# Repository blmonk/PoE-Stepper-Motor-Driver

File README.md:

# PoE-Stepper-Motor-Driver
ECE445 Senior Design

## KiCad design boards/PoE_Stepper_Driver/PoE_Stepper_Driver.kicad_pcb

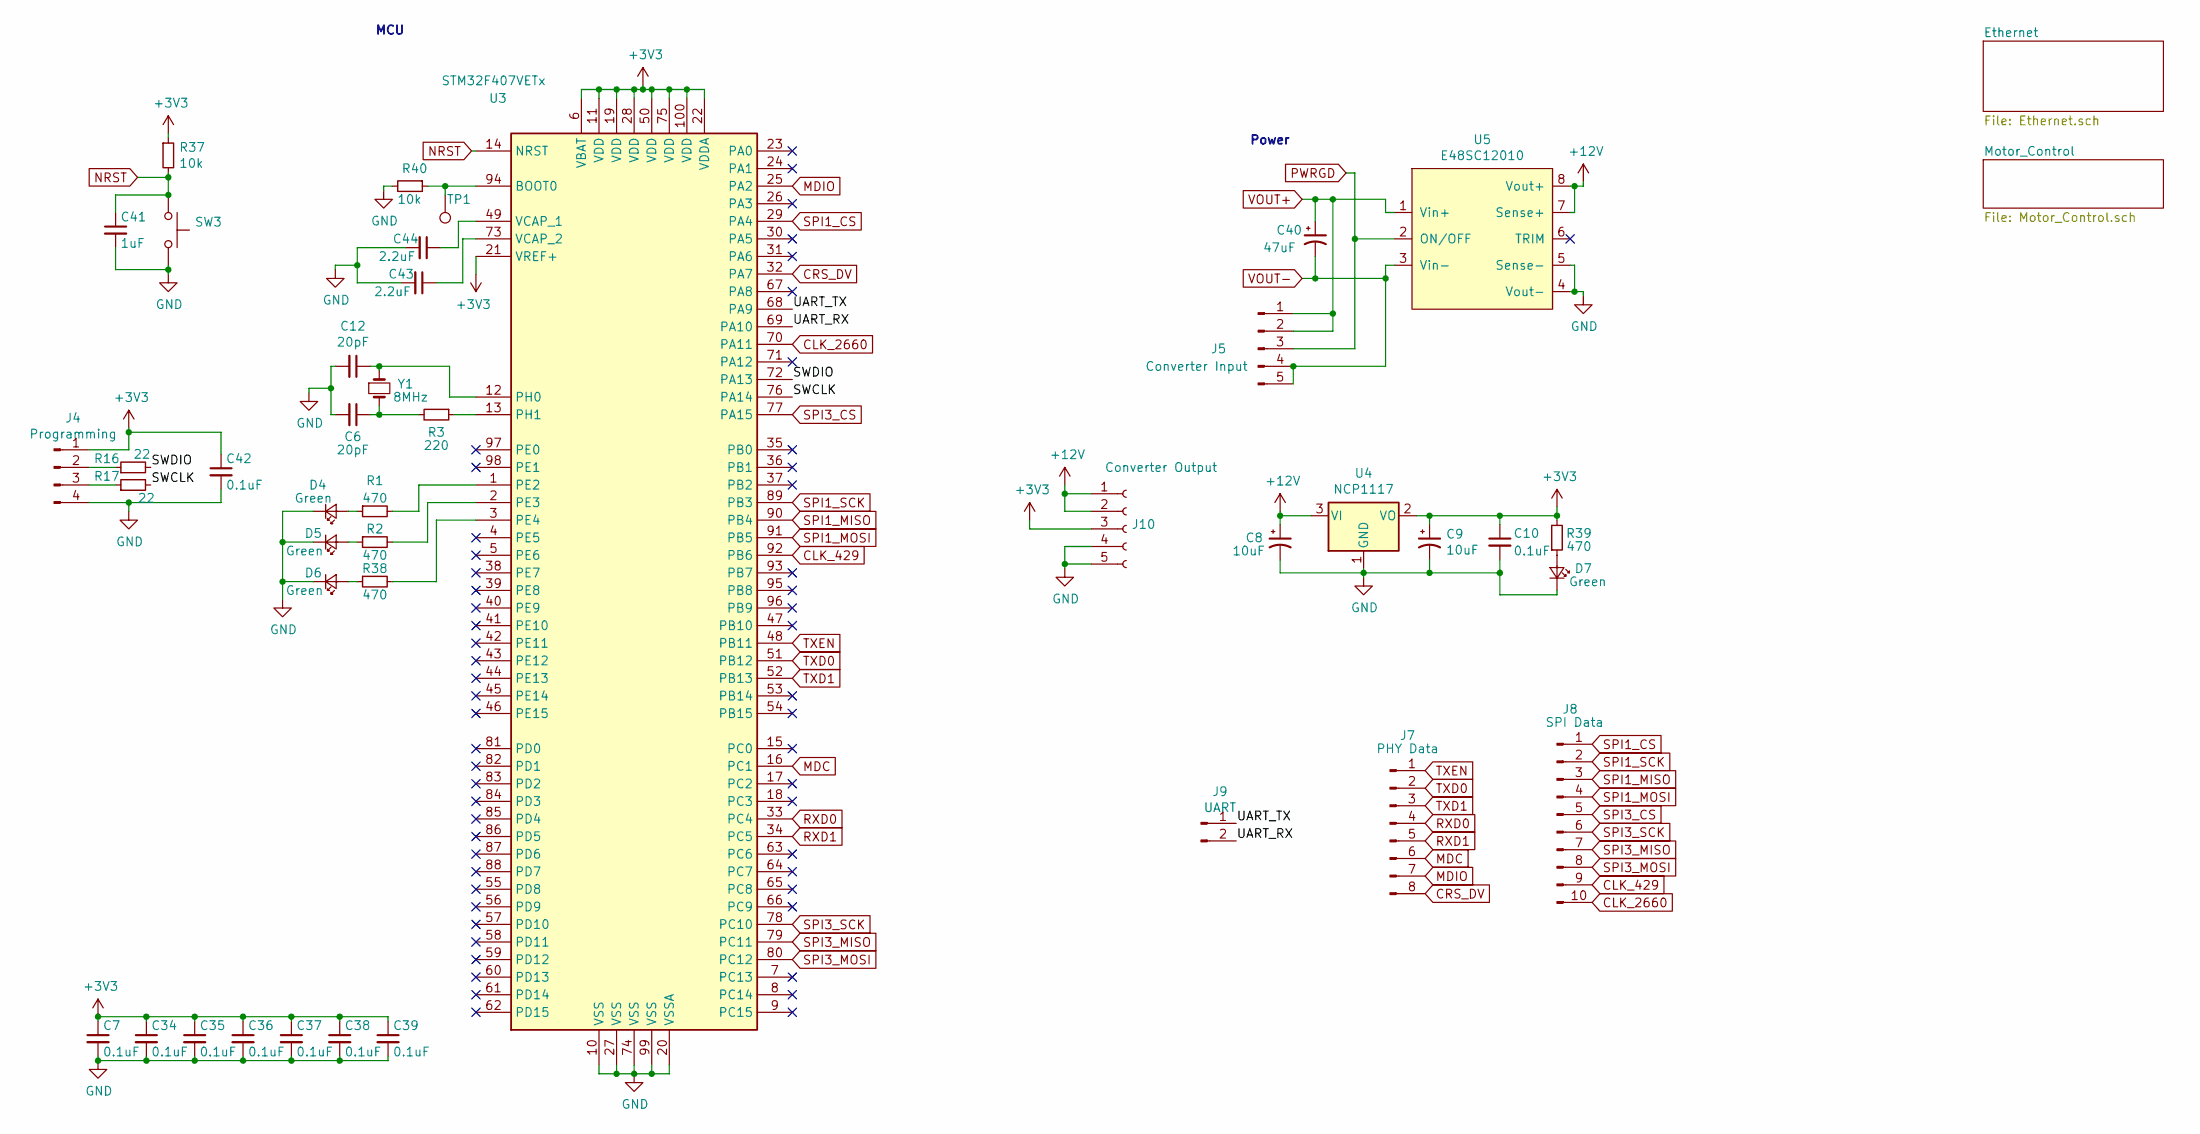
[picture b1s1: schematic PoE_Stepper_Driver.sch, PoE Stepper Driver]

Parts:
C6, C12: 20pF; C_0603_1608Metric_Pad1.05x0.95mm_HandSolder
C7, C10, C34, C35, C36, C37, C38, C39, C42: 0.1uF; C_0805_2012Metric_Pad1.15x1.40mm_HandSolder
C8, C9: 10uF; CP_Elec_6.3x5.4
C40: 47uF; CP_Radial_D8.0mm_P3.50mm
C41: 1uF; C_0805_2012Metric_Pad1.15x1.40mm_HandSolder
C43, C44: 2.2uF; C_0603_1608Metric_Pad1.05x0.95mm_HandSolder
D4, D5, D6, D7: Green; LED_0805_2012Metric_Pad1.15x1.40mm_HandSolder
J4: Programming; PinHeader_1x04_P2.54mm_Vertical
J5: Converter Input; PinHeader_1x05_P2.54mm_Vertical
J7: PHY Data; PinHeader_2x04_P2.54mm_Vertical
J8: SPI Data; PinHeader_2x05_P2.54mm_Vertical
J9: UART; PinHeader_1x02_P2.54mm_Vertical
J10: Converter Output; PinHeader_1x05_P2.54mm_Vertical
R1, R2, R38, R39: 470; R_0805_2012Metric_Pad1.15x1.40mm_HandSolder
R3: 220; R_0603_1608Metric_Pad1.05x0.95mm_HandSolder
R16, R17: 22; R_0805_2012Metric_Pad1.15x1.40mm_HandSolder
R37, R40: 10k; R_0805_2012Metric_Pad1.15x1.40mm_HandSolder
SW3: SW_Push; SW_SPST_B3S-1000
TP1: BOOT0; TestPoint_Pad_1.0x1.0mm
U3: STM32F407VETx; LQFP-100_14x14mm_P0.5mm
U4: NCP1117; SOT-223-3_TabPin2
U5: E48SC12010
Y1: 8MHz; Crystal_HC49-4H_Vertical

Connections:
+3V3: C7.1, C9.1, C10.1, C34.1, C35.1, C36.1, C37.1, C38.1, C39.1, C42.1, J4.1, J10.3, R37.1, R39.2, U3.6 (VBAT), U3.11 (VDD), U3.19 (VDD), U3.21 (VREF+), U3.22 (VDDA), U3.28 (VDD), U3.50 (VDD), U3.75 (VDD), U3.100 (VDD), U4.2 (VO); also elsewhere on the board
+12V: C8.1, J10.1, J10.2, U4.3 (VI), U5.7 (Sense+), U5.8 (Vout+); also elsewhere on the board
/SWCLK: R17.2, U3.76 (PA14)
/SWDIO: R16.2, U3.72 (PA13)
/UART_RX: J9.2, U3.69 (PA10)
/UART_TX: J9.1, U3.68 (PA9)
CLK_429: J8.9, U3.92 (PB6); also elsewhere on the board
CLK_2660: J8.10, U3.70 (PA11); also elsewhere on the board
CRS_DV: J7.8, U3.32 (PA7); also elsewhere on the board
GND: C6.2, C7.2, C8.2, C9.2, C10.2, C12.2, C34.2, C35.2, C36.2, C37.2, C38.2, C39.2, C41.2, C42.2, C43.2, C44.2, D4.1 (K), D5.1 (K), D6.1 (K), D7.1 (K), J4.4, J10.4, J10.5, R40.2, SW3.2, U3.10 (VSS), U3.20 (VSSA), U3.27 (VSS), U3.74 (VSS), U3.99 (VSS), U4.1 (GND), U5.4 (Vout-), U5.5 (Sense-); also elsewhere on the board
MDC: J7.6, U3.16 (PC1); also elsewhere on the board
MDIO: J7.7, U3.25 (PA2); also elsewhere on the board
NRST: C41.1, R37.2, SW3.1, U3.14 (NRST); also elsewhere on the board
unnamed: C6.1, R3.2, Y1.2
unnamed: C12.1, U3.12 (PH0), Y1.1
unnamed: C43.1, U3.73 (VCAP_2)
unnamed: C44.1, U3.49 (VCAP_1)
unnamed: D4.2 (A), R1.1
unnamed: D5.2 (A), R2.1
unnamed: D6.2 (A), R38.1
unnamed: D7.2 (A), R39.1
unnamed: J4.2, R16.1
unnamed: J4.3, R17.1
unnamed: R1.2, U3.1 (PE2)
unnamed: R2.2, U3.2 (PE3)
unnamed: R3.1, U3.13 (PH1)
unnamed: R38.2, U3.3 (PE4)
unnamed: R40.1, TP1.1, U3.94 (BOOT0)
PWRGD: J5.3, U5.2 (ON/OFF); also elsewhere on the board
RXD0: J7.4, U3.33 (PC4); also elsewhere on the board
RXD1: J7.5, U3.34 (PC5); also elsewhere on the board
SPI1_CS: J8.1, U3.29 (PA4); also elsewhere on the board
SPI1_MISO: J8.3, U3.90 (PB4); also elsewhere on the board
SPI1_MOSI: J8.4, U3.91 (PB5); also elsewhere on the board
SPI1_SCK: J8.2, U3.89 (PB3); also elsewhere on the board
TXD0: J7.2, U3.51 (PB12); also elsewhere on the board
TXD1: J7.3, U3.52 (PB13); also elsewhere on the board
TXEN: J7.1, U3.48 (PB11); also elsewhere on the board
VOUT+: C40.1, J5.1, J5.2, U5.1 (Vin+); also elsewhere on the board
VOUT-: C40.2, J5.4, J5.5, U5.3 (Vin-); also elsewhere on the board

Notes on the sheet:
Power
MCU

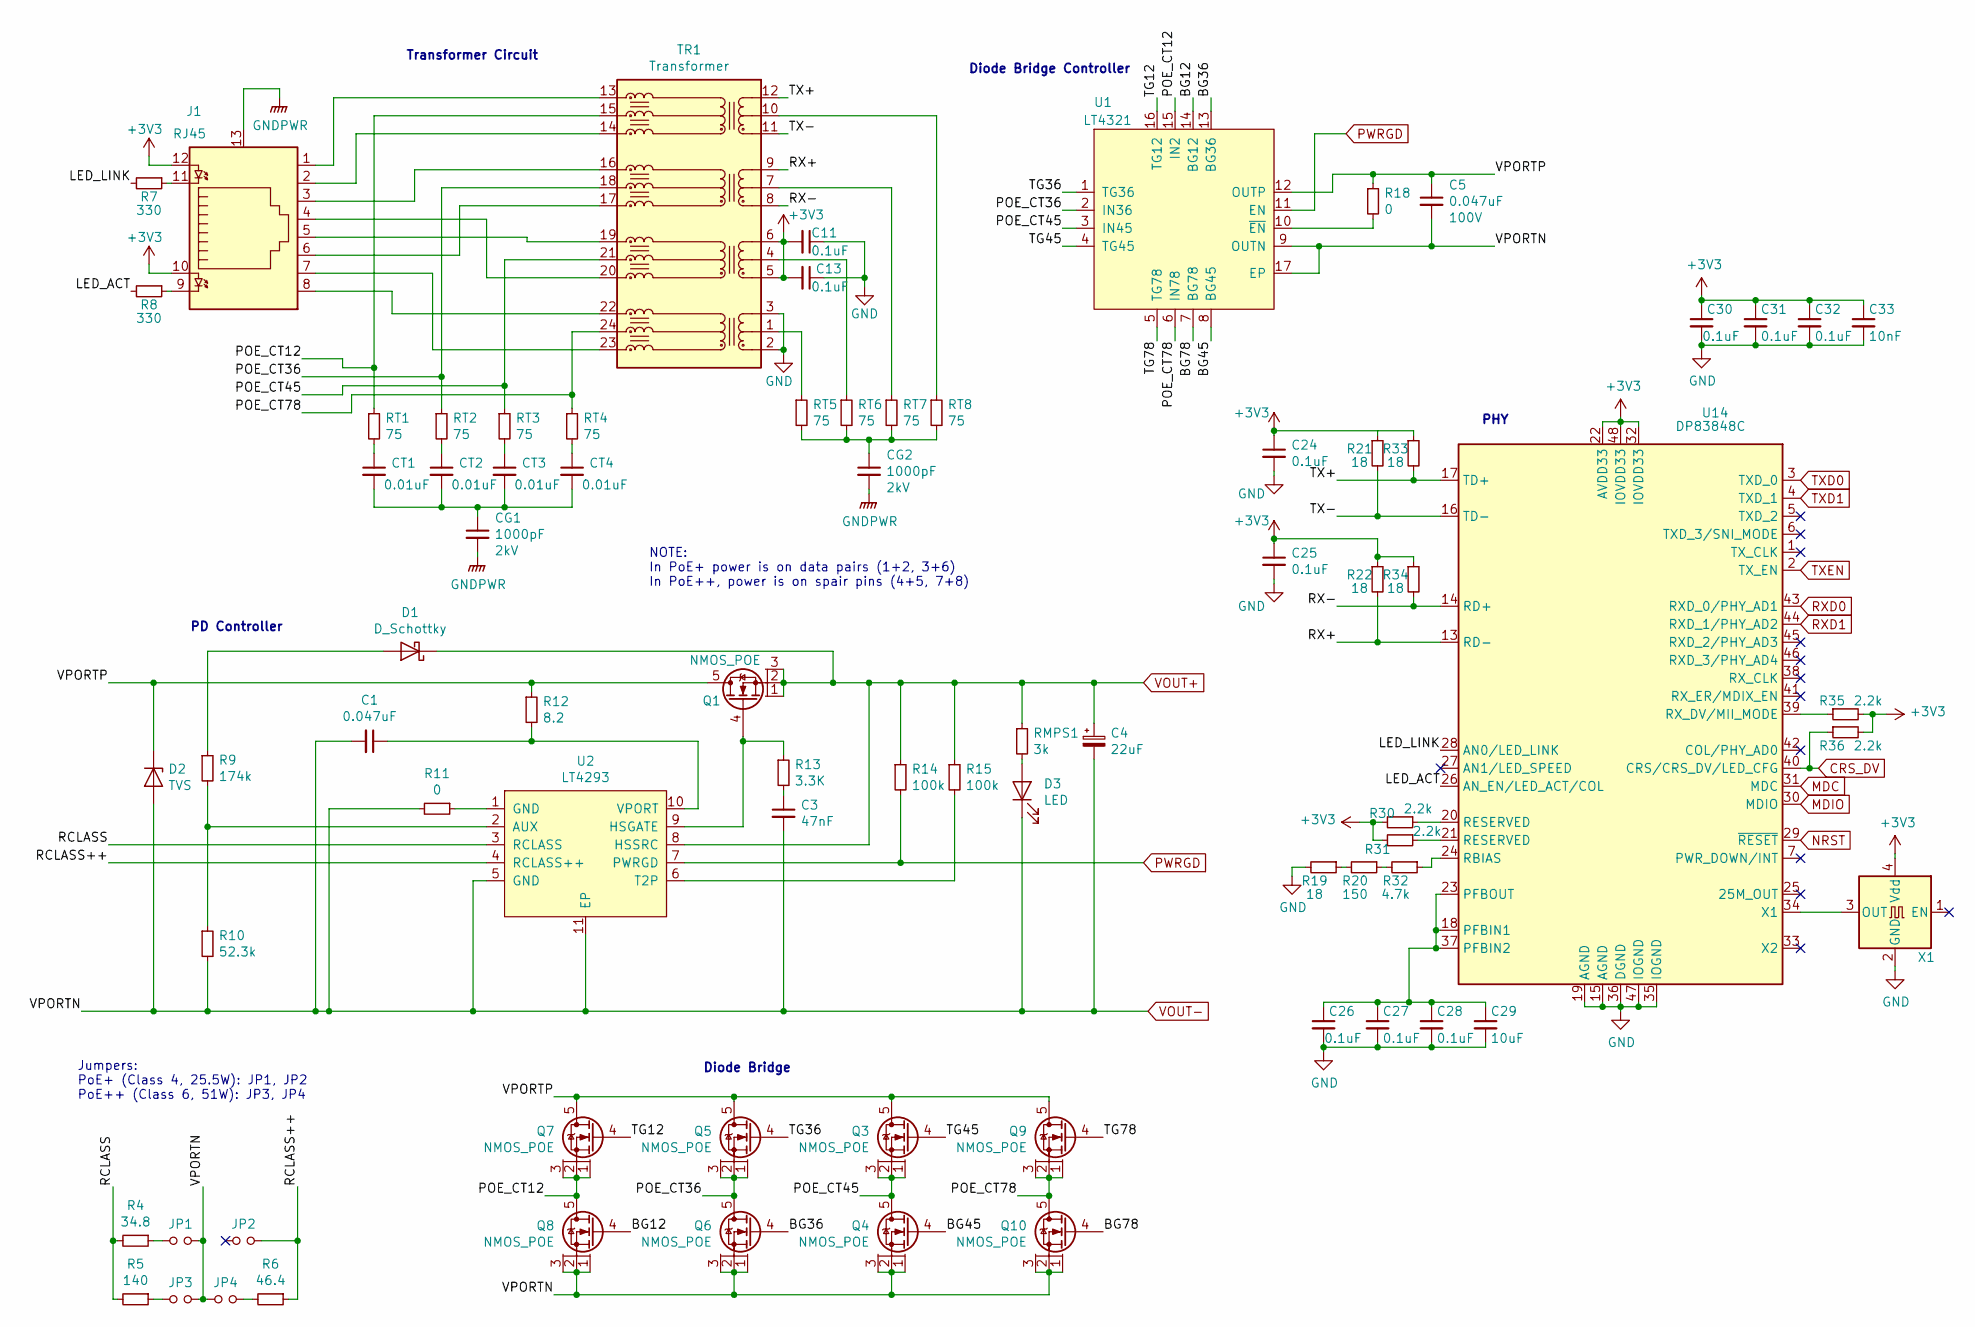
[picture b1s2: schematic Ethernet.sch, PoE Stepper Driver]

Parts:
C1: 0.047uF; C_0603_1608Metric_Pad1.05x0.95mm_HandSolder
C3: 47nF; C_0805_2012Metric_Pad1.15x1.40mm_HandSolder
C4: 22uF; CP_Elec_8x10.5
C5: 0.047uF; C_0603_1608Metric_Pad1.05x0.95mm_HandSolder; Voltage 100V
C11, C13, C24, C25, C26, C27, C28, C30, C31, C32: 0.1uF; C_0805_2012Metric_Pad1.15x1.40mm_HandSolder
C29: 10uF; C_0805_2012Metric_Pad1.15x1.40mm_HandSolder
C33: 10nF; C_0805_2012Metric_Pad1.15x1.40mm_HandSolder
CG1, CG2: 1000pF; C_1812_4532Metric_Pad1.30x3.40mm_HandSolder; Voltage 2kV
CT1, CT2, CT3, CT4: 0.01uF; C_0805_2012Metric_Pad1.15x1.40mm_HandSolder
D1: D_Schottky; D_SOD-128
D2: TVS; D_SOD-128
D3: LED; LED_0805_2012Metric_Pad1.15x1.40mm_HandSolder
J1: RJ45; RJ45_Amphenol_RJMG1BD3B8K1ANR
JP1, JP2, JP3, JP4: Jumper_NO_Small; PinHeader_1x02_P2.54mm_Vertical
Q1, Q3, Q4, Q5, Q6, Q7, Q8, Q9, Q10: NMOS_POE; LFPAK33
R4: 34.8; R_0805_2012Metric_Pad1.15x1.40mm_HandSolder
R5: 140; R_0805_2012Metric_Pad1.15x1.40mm_HandSolder
R6: 46.4; R_0805_2012Metric_Pad1.15x1.40mm_HandSolder
R7, R8: 330; R_0805_2012Metric_Pad1.15x1.40mm_HandSolder
R9: 174k; R_0603_1608Metric_Pad1.05x0.95mm_HandSolder
R10: 52.3k; R_0603_1608Metric_Pad1.05x0.95mm_HandSolder
R11, R18: 0; R_0603_1608Metric_Pad1.05x0.95mm_HandSolder
R12: 8.2; R_0805_2012Metric_Pad1.15x1.40mm_HandSolder
R13: 3.3K; R_0603_1608Metric_Pad1.05x0.95mm_HandSolder
R14, R15: 100k; R_0603_1608Metric_Pad1.05x0.95mm_HandSolder
R19, R21, R22, R33, R34: 18; R_0805_2012Metric_Pad1.15x1.40mm_HandSolder
R20: 150; R_0805_2012Metric_Pad1.15x1.40mm_HandSolder
R30, R31, R35, R36: 2.2k; R_0805_2012Metric_Pad1.15x1.40mm_HandSolder
R32: 4.7k; R_0805_2012Metric_Pad1.15x1.40mm_HandSolder
RMPS1: 3k; R_2512_6332Metric_Pad1.52x3.35mm_HandSolder
RT1, RT2, RT3, RT4, RT5, RT6, RT7, RT8: 75; R_0603_1608Metric_Pad1.05x0.95mm_HandSolder
TR1: Transformer; PoE_Transformer
U1: LT4321; QFN-16-1EP_4x4mm_P0.65mm_EP2.15x2.15mm
U2: LT4293; MSOP-10_3x3mm_P0.5mm
U14: DP83848C; LQFP-48_7x7mm_P0.5mm
X1: SXO53C

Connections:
+3V3: C11.2, C13.2, C24.1, C25.1, C30.1, C31.1, C32.1, C33.1, J1.10, J1.12, R21.1, R22.1, R30.2, R31.2, R33.1, R34.1, R35.2, R36.2, TR1.5 (TD2+), TR1.6 (TD2-), U14.22 (AVDD33), U14.32 (IOVDD33), U14.48 (IOVDD33), X1.4 (Vdd); also elsewhere on the board
/Ethernet/BG12: Q8.4, U1.14 (BG12)
/Ethernet/BG36: Q6.4, U1.13 (BG36)
/Ethernet/BG45: Q4.4, U1.8 (BG45)
/Ethernet/BG78: Q10.4, U1.7 (BG78)
/Ethernet/LED_ACT: R8.2, U14.26 (AN_EN/LED_ACT/COL)
/Ethernet/LED_LINK: R7.2, U14.28 (AN0/LED_LINK)
/Ethernet/POE_CT12: Q7.1, Q7.2, Q7.3, Q8.5, RT1.1, TR1.15 (MCT4), U1.15 (IN2)
/Ethernet/POE_CT36: Q5.1, Q5.2, Q5.3, Q6.5, RT2.1, TR1.18 (MCT3), U1.2 (IN36)
/Ethernet/POE_CT45: Q3.1, Q3.2, Q3.3, Q4.5, RT3.1, TR1.21 (MCT2), U1.3 (IN45)
/Ethernet/POE_CT78: Q9.1, Q9.2, Q9.3, Q10.5, RT4.1, TR1.24 (MTC1), U1.6 (IN78)
/Ethernet/RCLASS: R4.2, R5.2, U2.3 (RCLASS)
/Ethernet/RCLASS++: JP2.2, R6.1, U2.4 (RCLASS++)
/Ethernet/RX+: R22.2, TR1.9 (TD3-), U14.13 (RD-)
/Ethernet/RX-: R34.2, TR1.8 (TD3+), U14.14 (RD+)
/Ethernet/TG12: Q7.4, U1.16 (TG12)
/Ethernet/TG36: Q5.4, U1.1 (TG36)
/Ethernet/TG45: Q3.4, U1.4 (TG45)
/Ethernet/TG78: Q9.4, U1.5 (TG78)
/Ethernet/TX+: R33.2, TR1.12 (TD4-), U14.17 (TD+)
/Ethernet/TX-: R21.2, TR1.11 (TD4+), U14.16 (TD-)
/Ethernet/VPORTP: C5.1, D2.1 (K), Q1.5, Q3.5, Q5.5, Q7.5, Q9.5, R12.1, R18.1, U1.12 (OUTP)
CRS_DV: R36.1, U14.40 (CRS/CRS_DV/LED_CFG); also elsewhere on the board
GND: C11.1, C13.1, C24.2, C25.2, C26.2, C27.2, C28.2, C29.2, C30.2, C31.2, C32.2, C33.2, R19.2, TR1.2 (TD1+), TR1.3 (TD1-), U14.15 (AGND), U14.19 (AGND), U14.35 (IOGND), U14.36 (DGND), U14.47 (IOGND), X1.2 (GND); also elsewhere on the board
GNDPWR: CG1.2, CG2.2, J1.13
MDC: U14.31 (MDC); also elsewhere on the board
MDIO: U14.30 (MDIO); also elsewhere on the board
NRST: U14.29 (~RESET~); also elsewhere on the board
unnamed: C1.1, R12.2, U2.10 (VPORT)
unnamed: C3.1, R13.2
unnamed: C26.1, C27.1, C28.1, C29.1, U14.18 (PFBIN1), U14.23 (PFBOUT), U14.37 (PFBIN2)
unnamed: CG1.1, CT1.2, CT2.2, CT3.2, CT4.2
unnamed: CG2.1, RT5.2, RT6.2, RT7.2, RT8.2
unnamed: CT1.1, RT1.2
unnamed: CT2.1, RT2.2
unnamed: CT3.1, RT3.2
unnamed: CT4.1, RT4.2
unnamed: D1.2 (A), R9.1
unnamed: D3.2 (A), RMPS1.2
unnamed: J1.1, TR1.13 (MX4-)
unnamed: J1.2, TR1.14 (MX4+)
unnamed: J1.3, TR1.16 (MTX3-)
unnamed: J1.4, TR1.20 (MTX2+)
unnamed: J1.5, TR1.19 (MTX2-)
unnamed: J1.6, TR1.17 (MTX3+)
unnamed: J1.7, TR1.23 (MTX1+)
unnamed: J1.8, TR1.22 (MTX1-)
unnamed: J1.9, R8.1
unnamed: J1.11, R7.1
unnamed: JP1.1, R4.1
unnamed: JP3.1, R5.1
unnamed: JP4.2, R6.2
unnamed: Q1.4, R13.1, U2.9 (HSGATE)
unnamed: R9.2, R10.1, U2.2 (AUX)
unnamed: R11.1, U2.1 (GND)
unnamed: R15.2, U2.6 (T2P)
unnamed: R18.2, U1.10 (~EN)
unnamed: R19.1, R20.2
unnamed: R20.1, R32.2
unnamed: R30.1, U14.20 (RESERVED)
unnamed: R31.1, U14.21 (RESERVED)
unnamed: R32.1, U14.24 (RBIAS)
unnamed: R35.1, U14.39 (RX_DV/MII_MODE)
unnamed: RT5.1, TR1.1 (TCT1)
unnamed: RT6.1, TR1.4 (TCT2)
unnamed: RT7.1, TR1.7 (TCT3)
unnamed: RT8.1, TR1.10 (TCT4)
unnamed: U14.34 (X1), X1.3 (OUT)
PWRGD: R14.2, U1.11 (EN), U2.7 (PWRGD); also elsewhere on the board
RXD0: U14.43 (RXD_0/PHY_AD1); also elsewhere on the board
RXD1: U14.44 (RXD_1/PHY_AD2); also elsewhere on the board
TXD0: U14.3 (TXD_0); also elsewhere on the board
TXD1: U14.4 (TXD_1); also elsewhere on the board
TXEN: U14.2 (TX_EN); also elsewhere on the board
VOUT+: C4.1, D1.1 (K), Q1.1, Q1.2, Q1.3, R14.1, R15.1, RMPS1.1, U2.8 (HSSRC); also elsewhere on the board
VOUT-: C1.2, C3.2, C4.2, C5.2, D2.2 (A), D3.1 (K), JP1.2, JP3.2, JP4.1, Q4.1, Q4.2, Q4.3, Q6.1, Q6.2, Q6.3, Q8.1, Q8.2, Q8.3, Q10.1, Q10.2, Q10.3, R10.2, R11.2, U1.9 (OUTN), U1.17 (EP), U2.5 (GND), U2.11 (EP); also elsewhere on the board

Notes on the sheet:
Jumpers: PoE+ (Class 4, 25.5W): JP1, JP2 PoE++ (Class 6, 51W): JP3, JP4
Diode Bridge Controller
Transformer Circuit
PD Controller
Diode Bridge
NOTE: In PoE+ power is on data pairs (1+2, 3+6) In PoE++, power is on spair pins (4+5, 7+8)
PHY

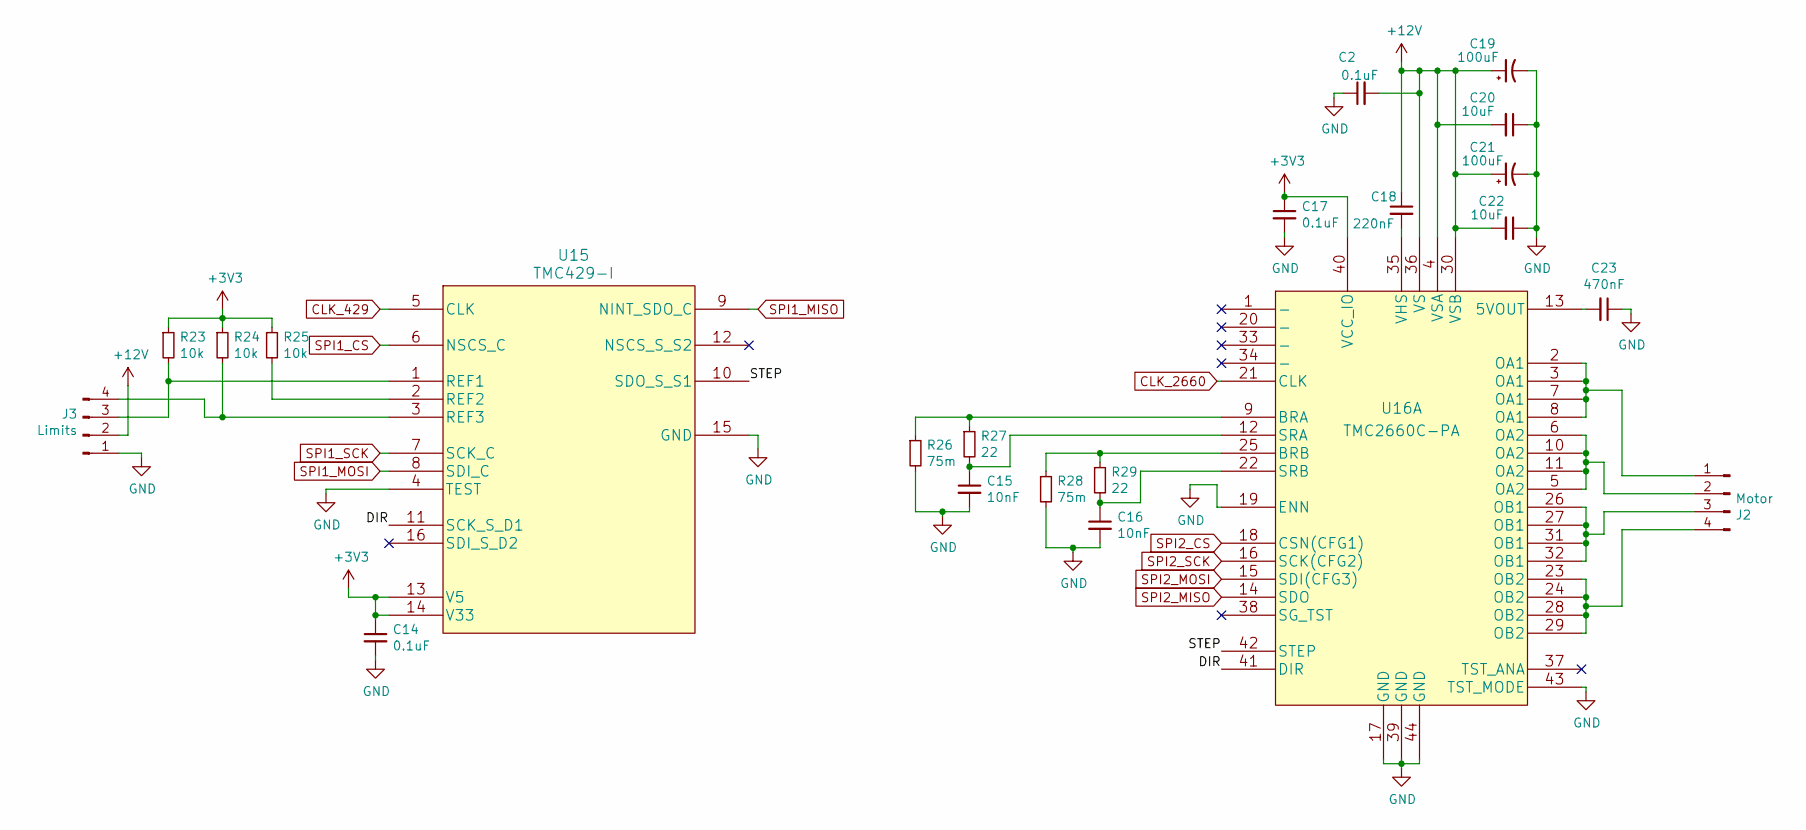
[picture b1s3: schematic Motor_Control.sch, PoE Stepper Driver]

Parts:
C2, C14, C17: 0.1uF; C_0805_2012Metric_Pad1.15x1.40mm_HandSolder
C15, C16: 10nF; C_0805_2012Metric_Pad1.15x1.40mm_HandSolder
C18: 220nF; C_0805_2012Metric_Pad1.15x1.40mm_HandSolder
C19, C21: 100uF; CP_Radial_D8.0mm_P3.50mm
C20, C22: 10uF; C_1206_3216Metric_Pad1.42x1.75mm_HandSolder
C23: 470nF; C_0805_2012Metric_Pad1.15x1.40mm_HandSolder
J2: Motor; JST_PH_B4B-PH-K_1x04_P2.00mm_Vertical
J3: Limits; JST_PH_B4B-PH-K_1x04_P2.00mm_Vertical
R23, R24, R25: 10k; R_0805_2012Metric_Pad1.15x1.40mm_HandSolder
R26, R28: 75m; R_2010_5025Metric_Pad1.52x2.65mm_HandSolder
R27, R29: 22; R_0805_2012Metric_Pad1.15x1.40mm_HandSolder
U15: TMC429-I; SSOP-16_3.9x4.9mm_P0.635mm
U16: TMC2660C-PA; PQFP-44_10x10mm_P0.8mm

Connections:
+3V3: C14.1, C17.1, R23.1, R24.1, R25.1, U15.13 (V5), U15.14 (V33), U16.40 (VCC_IO); also elsewhere on the board
+12V: C2.2, C18.1, C19.1, C20.2, C21.1, C22.2, J3.2, U16.4 (VSA), U16.30 (VSB), U16.36 (VS); also elsewhere on the board
/Motor_Control/DIR: U15.11 (SCK_S_D1), U16.41 (DIR)
/Motor_Control/STEP: U15.10 (SDO_S_S1), U16.42 (STEP)
CLK_429: U15.5 (CLK); also elsewhere on the board
CLK_2660: U16.21 (CLK); also elsewhere on the board
GND: C2.1, C14.2, C15.2, C16.2, C17.2, C19.2, C20.1, C21.2, C22.1, C23.1, J3.1, R26.2, R28.2, U15.4 (TEST), U15.15 (GND), U16.17 (GND), U16.19 (ENN), U16.39 (GND), U16.43 (TST_MODE), U16.44 (GND); also elsewhere on the board
unnamed: C15.1, R27.2, U16.12 (SRA)
unnamed: C16.1, R29.2, U16.22 (SRB)
unnamed: C18.2, U16.35 (VHS)
unnamed: C23.2, U16.13 (5VOUT)
unnamed: J2.1, U16.2 (OA1), U16.3 (OA1), U16.7 (OA1), U16.8 (OA1)
unnamed: J2.2, U16.5 (OA2), U16.6 (OA2), U16.10 (OA2), U16.11 (OA2)
unnamed: J2.3, U16.26 (OB1), U16.27 (OB1), U16.31 (OB1), U16.32 (OB1)
unnamed: J2.4, U16.23 (OB2), U16.24 (OB2), U16.28 (OB2), U16.29 (OB2)
unnamed: J3.3, R23.2, U15.1 (REF1)
unnamed: J3.4, R24.2, U15.3 (REF3)
unnamed: R25.2, U15.2 (REF2)
unnamed: R26.1, R27.1, U16.9 (BRA)
unnamed: R28.1, R29.1, U16.25 (BRB)
SPI1_CS: U15.6 (NSCS_C); also elsewhere on the board
SPI1_MISO: U15.9 (NINT_SDO_C); also elsewhere on the board
SPI1_MOSI: U15.8 (SDI_C); also elsewhere on the board
SPI1_SCK: U15.7 (SCK_C); also elsewhere on the board

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
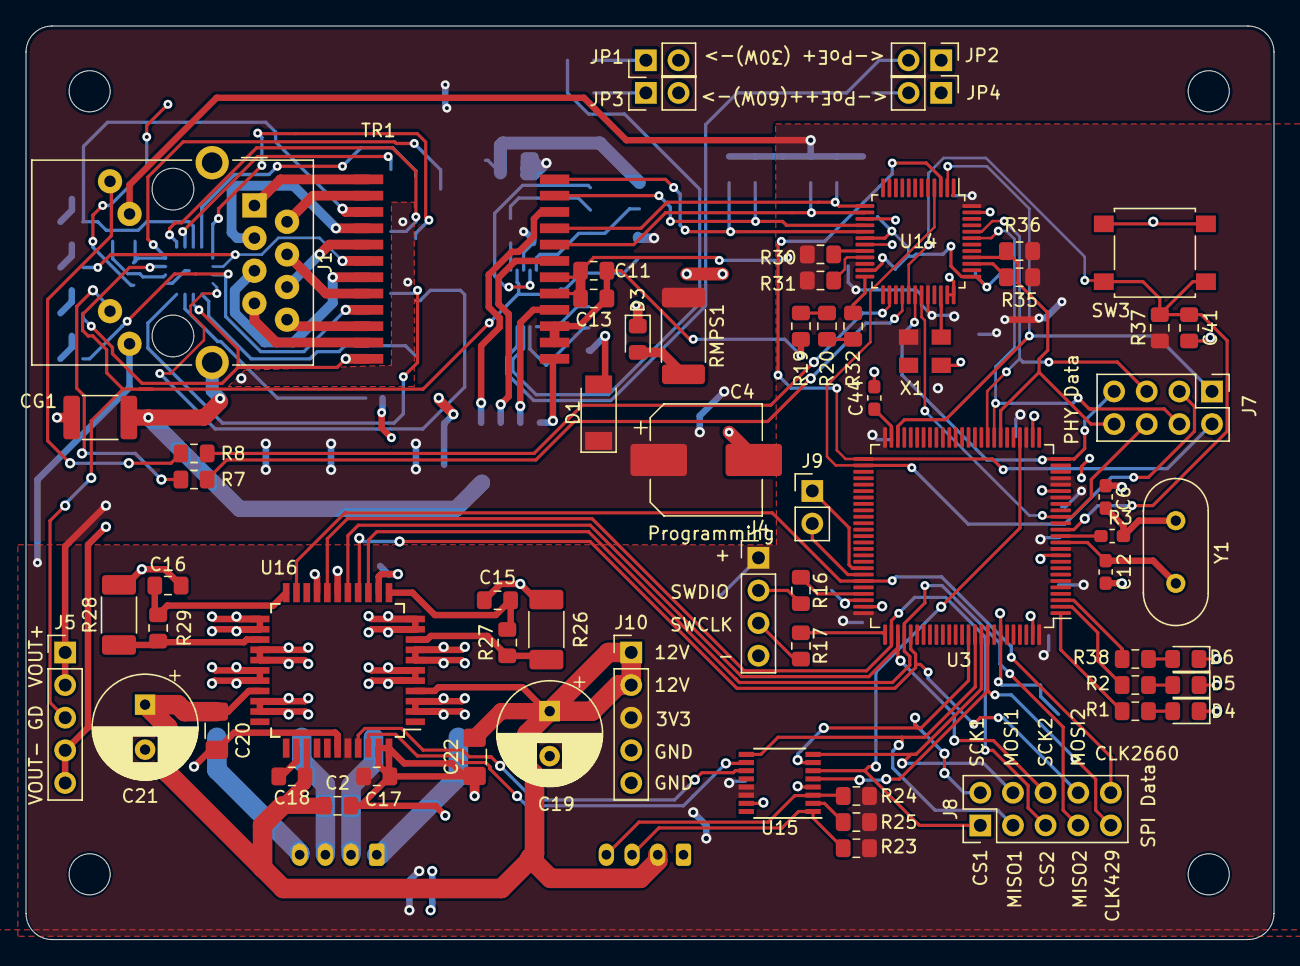
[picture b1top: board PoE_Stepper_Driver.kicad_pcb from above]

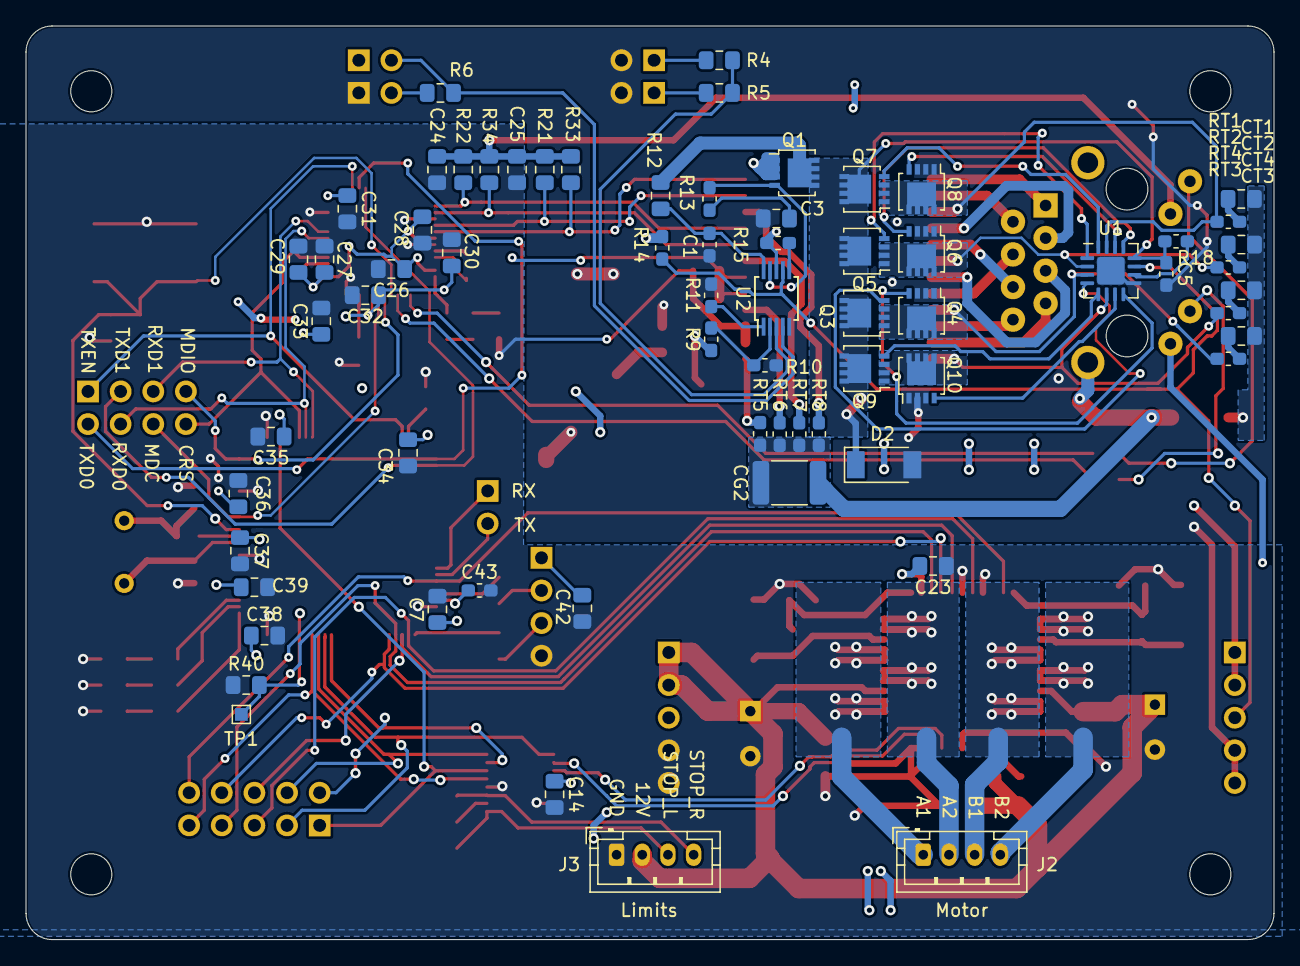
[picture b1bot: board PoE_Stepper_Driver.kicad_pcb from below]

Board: 2 copper layers, 97.2 x 71.1 mm, 133 parts (68 on the bottom side), 120 nets.

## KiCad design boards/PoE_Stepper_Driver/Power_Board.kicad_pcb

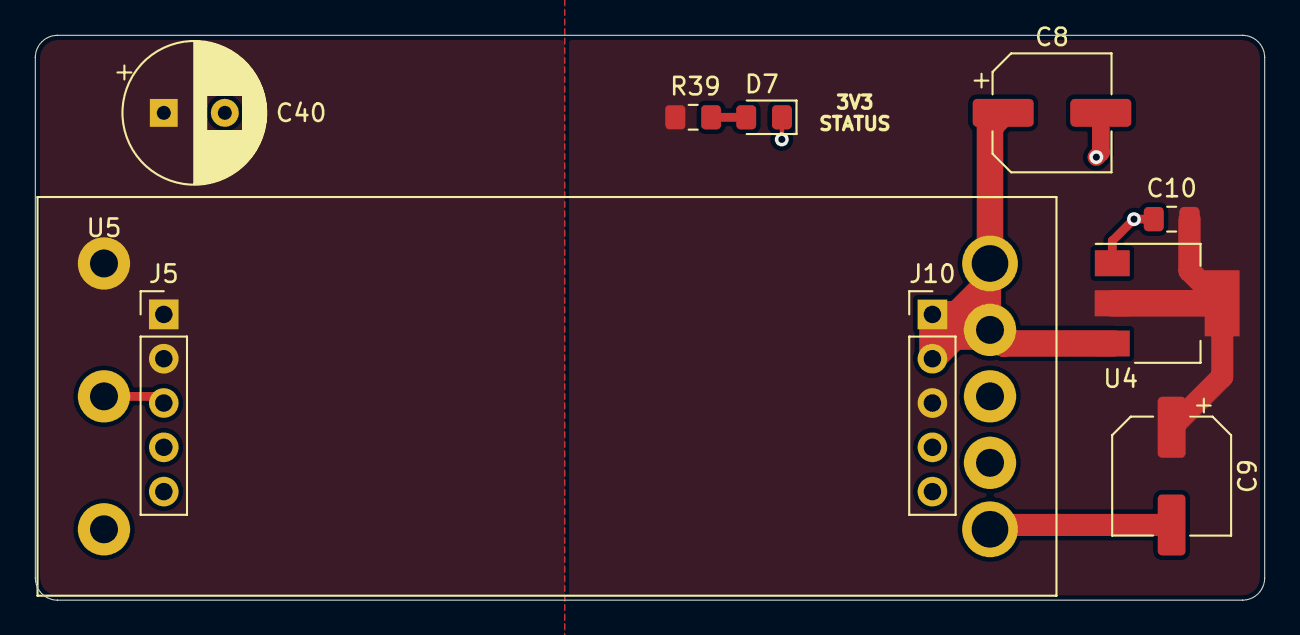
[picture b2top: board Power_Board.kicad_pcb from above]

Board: 2 copper layers, 70.5 x 32.4 mm, 10 parts (0 on the bottom side), 7 nets.

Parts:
C8, C9: 10uF; CP_Elec_6.3x5.4
C10: 0.1uF; C_0805_2012Metric_Pad1.15x1.40mm_HandSolder
C40: 47uF; CP_Radial_D8.0mm_P3.50mm
D7: Green; LED_0805_2012Metric_Pad1.15x1.40mm_HandSolder
J5: Converter Input; PinHeader_1x05_P2.54mm_Vertical
J10: Converter Output; PinHeader_1x05_P2.54mm_Vertical
R39: 470; R_0805_2012Metric_Pad1.15x1.40mm_HandSolder
U4: NCP1117; SOT-223-3_TabPin2
U5: E48SC12010

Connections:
+3V3: C9.1, C10.1, J10.3, R39.2, U4.2
+12V: C8.1, J10.1, J10.2, U4.3, U5.7, U5.8
GND: C8.2, C9.2, C10.2, D7.1, J10.4, J10.5, U4.1, U5.4, U5.5
unnamed: D7.2, R39.1
PWRGD: J5.3, U5.2
VOUT+: C40.1, J5.1, J5.2, U5.1
VOUT-: C40.2, J5.4, J5.5, U5.3

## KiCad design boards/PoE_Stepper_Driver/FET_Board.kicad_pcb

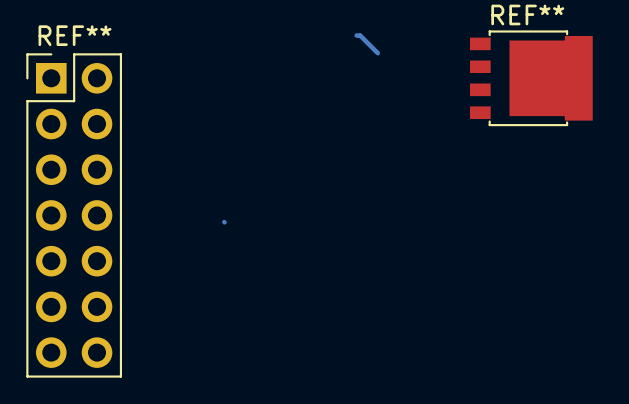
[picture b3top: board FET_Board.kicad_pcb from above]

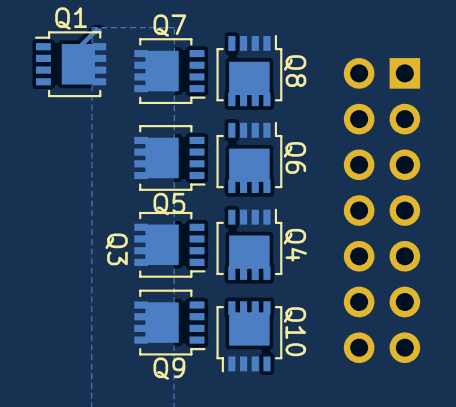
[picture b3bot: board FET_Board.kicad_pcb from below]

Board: 2 copper layers, 9 parts (9 on the bottom side), 7 nets.

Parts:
Q1, Q3, Q4, Q5, Q6, Q7, Q8, Q9, Q10: NMOS_POE; LFPAK33

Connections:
/Ethernet/POE_CT12: Q7.1, Q7.2, Q7.3, Q8.5
/Ethernet/POE_CT36: Q5.1, Q5.2, Q5.3, Q6.5
/Ethernet/POE_CT45: Q3.1, Q3.2, Q3.3, Q4.5
/Ethernet/POE_CT78: Q9.1, Q9.2, Q9.3, Q10.5
/Ethernet/VPORTP: Q1.5, Q3.5, Q5.5, Q7.5, Q9.5
VOUT+: Q1.1, Q1.2, Q1.3
VOUT-: Q4.1, Q4.2, Q4.3, Q6.1, Q6.2, Q6.3, Q8.1, Q8.2, Q8.3, Q10.1, Q10.2, Q10.3

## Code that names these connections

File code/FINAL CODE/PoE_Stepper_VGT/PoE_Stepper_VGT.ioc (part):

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Mcu.Name=STM32F407V(E-G)Tx
Mcu.Package=LQFP100
Mcu.UserName=STM32F407VGTx
PA1.Mode=RMII
PA1.Signal=ETH_REF_CLK
PA10.Mode=Asynchronous
PA10.Signal=USART1_RX
PA13.Mode=Serial_Wire
PA13.Signal=SYS_JTMS-SWDIO
PA14.Mode=Serial_Wire
PA14.Signal=SYS_JTCK-SWCLK
PA15.GPIOParameters=GPIO_Label
PA15.GPIO_Label=SPI3_CS
PA15.Signal=GPIO_Output
PA2.Mode=RMII
PA2.Signal=ETH_MDIO
PA4.GPIOParameters=GPIO_Label
PA4.GPIO_Label=SPI1_CS
PA4.Signal=GPIO_Output
PA7.Mode=RMII
PA7.Signal=ETH_CRS_DV
PA9.Mode=Asynchronous
PA9.Signal=USART1_TX
PB11.Mode=RMII
PB11.Signal=ETH_TX_EN
PB12.Mode=RMII
PB12.Signal=ETH_TXD0
PB13.Mode=RMII
PB13.Signal=ETH_TXD1
PB3.Mode=Full_Duplex_Master
PB3.Signal=SPI1_SCK
PB4.Mode=Full_Duplex_Master
PB4.Signal=SPI1_MISO
PB5.Mode=Full_Duplex_Master
PB5.Signal=SPI1_MOSI
PB6.GPIOParameters=GPIO_Label
PB6.GPIO_Label=CLK_429
PB6.Signal=S_TIM4_CH1
PC1.Mode=RMII
PC1.Signal=ETH_MDC
PC10.Mode=Full_Duplex_Master
PC10.Signal=SPI3_SCK
PC11.Mode=Full_Duplex_Master
PC11.Signal=SPI3_MISO
PC12.Mode=Full_Duplex_Master
PC12.Signal=SPI3_MOSI
PC4.Mode=RMII
PC4.Signal=ETH_RXD0
PC5.Mode=RMII
PC5.Signal=ETH_RXD1
PE2.Signal=GPIO_Output
PE3.Signal=GPIO_Output
PE4.Signal=GPIO_Output
PH0-OSC_IN.Mode=HSE-External-Oscillator
PH0-OSC_IN.Signal=RCC_OSC_IN
PH1-OSC_OUT.Mode=HSE-External-Oscillator
PH1-OSC_OUT.Signal=RCC_OSC_OUT
RCC.HSE_VALUE=8000000
RCC.SYSCLKFreq_VALUE=128000000
RCC.SYSCLKSource=RCC_SYSCLKSOURCE_PLLCLK
board=custom

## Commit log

2022-02-02 added blmonk2 md file
2022-02-02 updated blmonk2 md file
2022-02-02 added folders and empty kicad project
2022-02-02 moved blmonk2 notebook file
2022-02-02 started schematic, added reference files for poe board
2022-02-02 started poe side of schematic
2022-02-17 added ethernet transformer
2022-02-18 almost done with ethernet schematic, need phy and annotations
2022-02-18 added trinamic chips
2022-02-21 pretty much finished motor subsystem schematic
2022-02-22 added phy schematic symbol
2022-02-22 added actual phy
2022-02-25 added dp83848 phy and more caps
2022-03-01 started board layout
2022-03-01 why tf is gnd connected to vout- bruhh
2022-03-02 fixed ground issue
2022-03-03 finished footprint assignment
2022-03-04 almost finished ethernet layout
2022-03-04 added programming pins
2022-03-04 burhhhhh sheeeeeeeeeeeeeeeeeesh
2022-03-05 Added motor control
2022-03-06 Revert "Added motor control"
    This reverts commit 7b2113a3a06210cf39fce9f6ba2f7b8593b46419.
2022-03-06 putting power on separate board
2022-03-06 finished power board
2022-03-06 finished power board fr
2022-03-06 done routing phy signals to mcu
2022-03-07 finished 2660 planes
2022-03-07 finished spi routing
2022-03-07 finished 1st draft of pcb
2022-03-08 added silkscreen info
2022-03-08 added UART
2022-03-08 fixed weird track
2022-03-08 created gerbers, passed audit
2022-03-08 added pwr board gerbers
2022-03-30 added working blink code
2022-03-30 added timers for trinamic clks
2022-03-31 made rev2 board changes
2022-04-10 got sprrintf to work with uart config
2022-04-17 writing to 429 is working
2022-04-19 moving to a postition but not correctly :(
2022-05-06 notebook migrated from doc to markdown
2022-05-06 added final code
2022-05-06 rindra to putra
2022-05-06 Delete notebooks/rindra directory
    delete rindra
2022-05-06 converted doc to markdown
2022-05-06 fixed markdown conversion
